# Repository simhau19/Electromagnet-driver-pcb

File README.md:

# Electromagnet-driver-pcb
[Schematics](Audiovisualizer%20PCB.pdf)

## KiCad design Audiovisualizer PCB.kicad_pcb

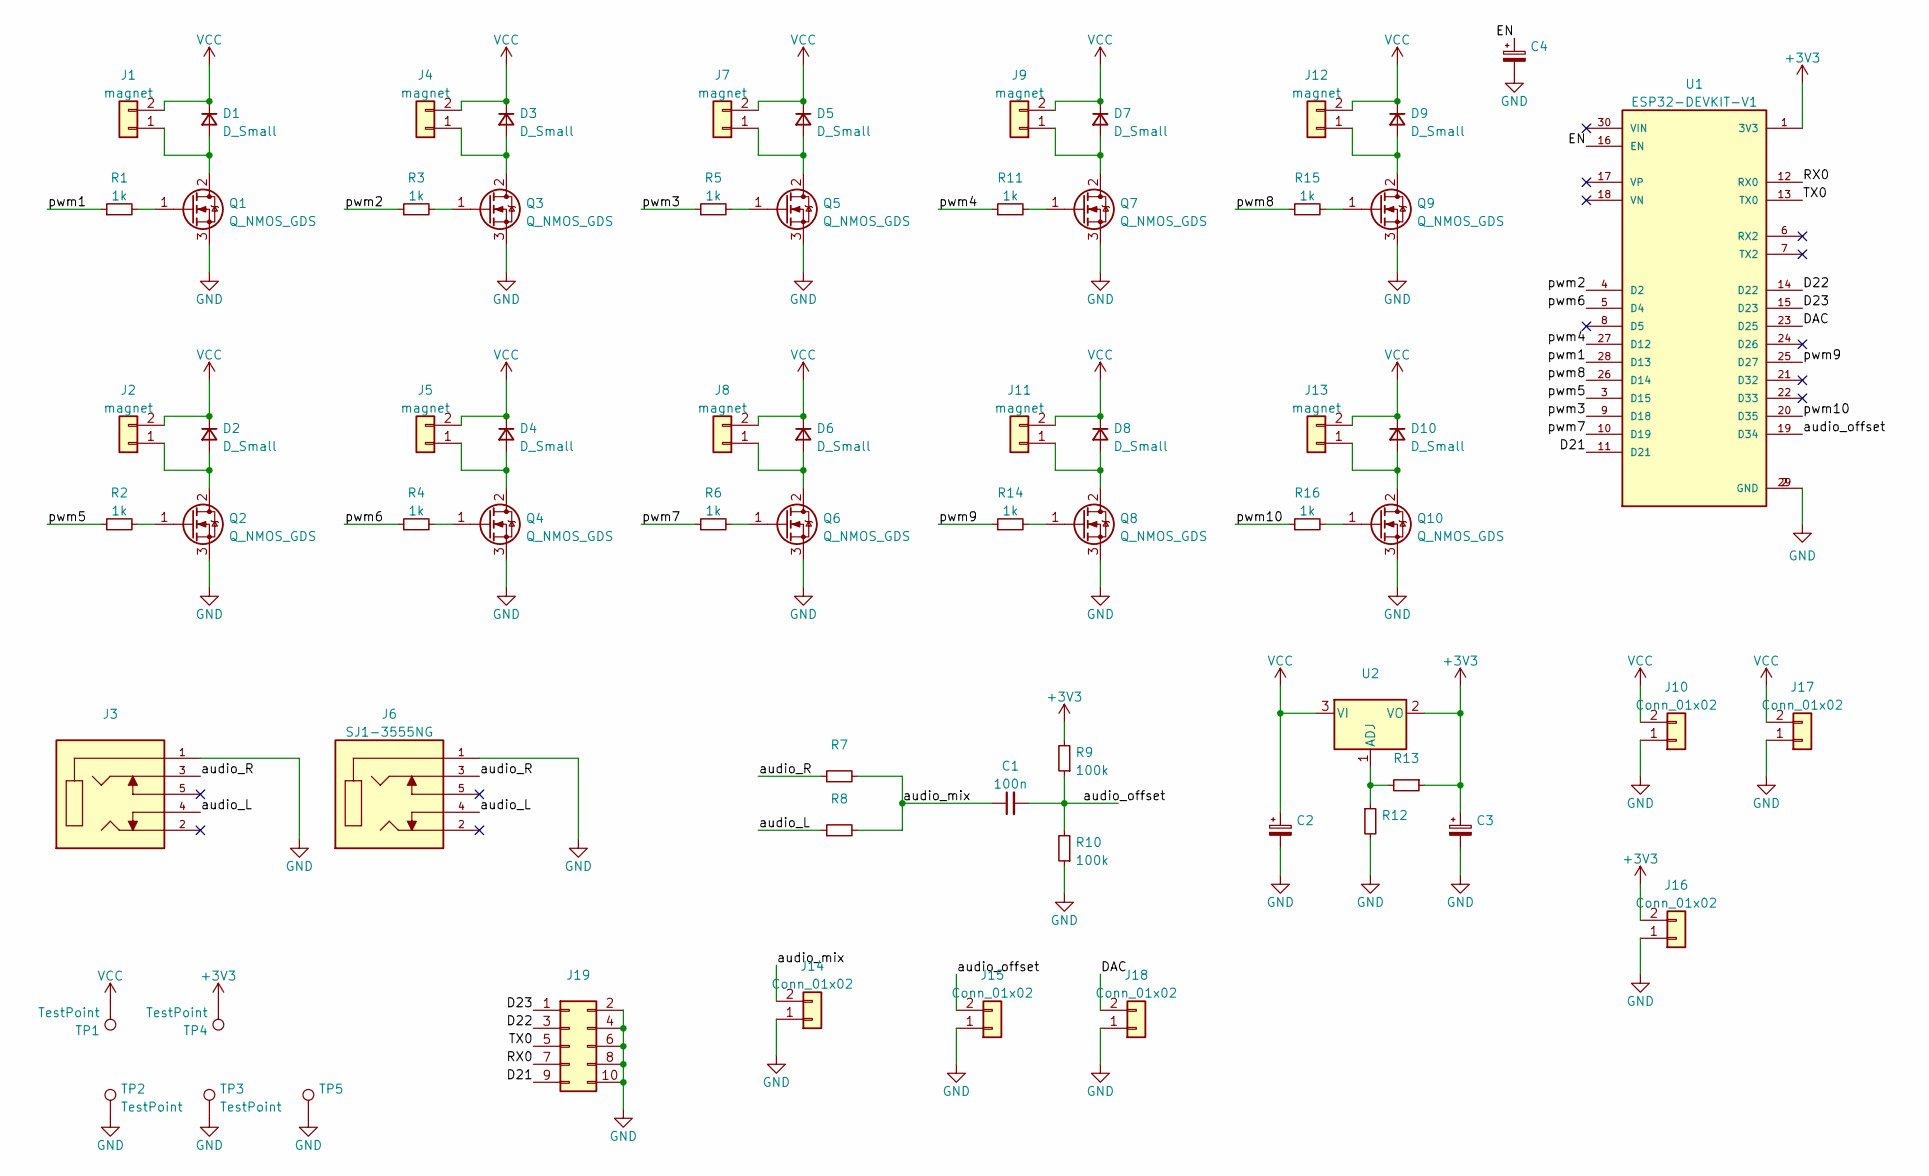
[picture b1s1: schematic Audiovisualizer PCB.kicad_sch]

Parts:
C1: 100n
C2, C3: (no value)
C4: CP_Radial_D6.3mm_P2.50mm
D1, D2, D3, D4, D5, D6, D7, D8, D9, D10: D_Small; D_A-405_P7.62mm_Horizontal
J1, J2, J4, J5, J7, J8, J9, J11, J12, J13: magnet; PinHeader_1x02_P2.54mm_Vertical
J3: PART_REV 1.0
J6: SJ1-3555NG; PART_REV 1.0
J10, J14, J15, J16, J18: Conn_01x02; PinHeader_1x02_P2.54mm_Vertical
J17: Conn_01x02
J19: (no value)
Q1, Q2, Q3, Q4, Q5, Q6, Q7, Q8, Q9, Q10: Q_NMOS_GDS; TO-220-3_Vertical
R1, R2, R3, R4, R5, R6, R11, R14, R15, R16: 1k; R_Axial_DIN0204_L3.6mm_D1.6mm_P7.62mm_Horizontal
R7, R8: R_Axial_DIN0204_L3.6mm_D1.6mm_P7.62mm_Horizontal
R9, R10: 100k; R_Axial_DIN0204_L3.6mm_D1.6mm_P7.62mm_Horizontal
R12, R13: (no value)
TP1, TP2, TP3, TP4: TestPoint
TP5: (no value)
U1: ESP32-DEVKIT-V1; MODULE_ESP32_DEVKIT_V1; PARTREV N/A
U2: (no value)

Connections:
+3V3: C3.1, J16.2, R9.2, R13.1, TP4.1, U1.1 (3V3), U2.2 (VO)
/D21: J19.9, U1.11 (D21)
/D22: J19.3, U1.14 (D22)
/D23: J19.1, U1.15 (D23)
/DAC: J18.2, U1.23 (D25)
/EN: C4.1, U1.16 (EN)
/RX0: J19.7, U1.12 (RX0)
/TX0: J19.5, U1.13 (TX0)
/audio_L: J3.4, J6.4, R8.1
/audio_R: J3.3, J6.3, R7.1
/audio_mix: C1.1, J14.2, R7.2, R8.2
/audio_offset: C1.2, J15.2, R9.1, R10.2, U1.19 (D34)
/pwm1: R1.1, U1.28 (D13)
/pwm2: R3.1, U1.4 (D2)
/pwm3: R5.1, U1.9 (D18)
/pwm4: R11.1, U1.27 (D12)
/pwm5: R2.1, U1.3 (D15)
/pwm6: R4.1, U1.5 (D4)
/pwm7: R6.1, U1.10 (D19)
/pwm8: R15.1, U1.26 (D14)
/pwm9: R14.1, U1.25 (D27)
/pwm10: R16.1, U1.20 (D35)
GND: C2.2, C3.2, C4.2, J3.1, J6.1, J10.1, J14.1, J15.1, J16.1, J17.1, J18.1, J19.2, J19.4, J19.6, J19.8, J19.10, Q1.3 (S), Q2.3 (S), Q3.3 (S), Q4.3 (S), Q5.3 (S), Q6.3 (S), Q7.3 (S), Q8.3 (S), Q9.3 (S), Q10.3 (S), R10.1, R12.2, TP2.1, TP3.1, TP5.1, U1.2 (GND), U1.29 (GND)
unnamed: D1.2 (A), J1.1, Q1.2 (D)
unnamed: D2.2 (A), J2.1, Q2.2 (D)
unnamed: D3.2 (A), J4.1, Q3.2 (D)
unnamed: D4.2 (A), J5.1, Q4.2 (D)
unnamed: D5.2 (A), J7.1, Q5.2 (D)
unnamed: D6.2 (A), J8.1, Q6.2 (D)
unnamed: D7.2 (A), J9.1, Q7.2 (D)
unnamed: D8.2 (A), J11.1, Q8.2 (D)
unnamed: D9.2 (A), J12.1, Q9.2 (D)
unnamed: D10.2 (A), J13.1, Q10.2 (D)
unnamed: Q1.1 (G), R1.2
unnamed: Q2.1 (G), R2.2
unnamed: Q3.1 (G), R3.2
unnamed: Q4.1 (G), R4.2
unnamed: Q5.1 (G), R5.2
unnamed: Q6.1 (G), R6.2
unnamed: Q7.1 (G), R11.2
unnamed: Q8.1 (G), R14.2
unnamed: Q9.1 (G), R15.2
unnamed: Q10.1 (G), R16.2
unnamed: R12.1, R13.2, U2.1 (ADJ)
VCC: C2.1, D1.1 (K), D2.1 (K), D3.1 (K), D4.1 (K), D5.1 (K), D6.1 (K), D7.1 (K), D8.1 (K), D9.1 (K), D10.1 (K), J1.2, J2.2, J4.2, J5.2, J7.2, J8.2, J9.2, J10.2, J11.2, J12.2, J13.2, J17.2, TP1.1, U2.3 (VI)

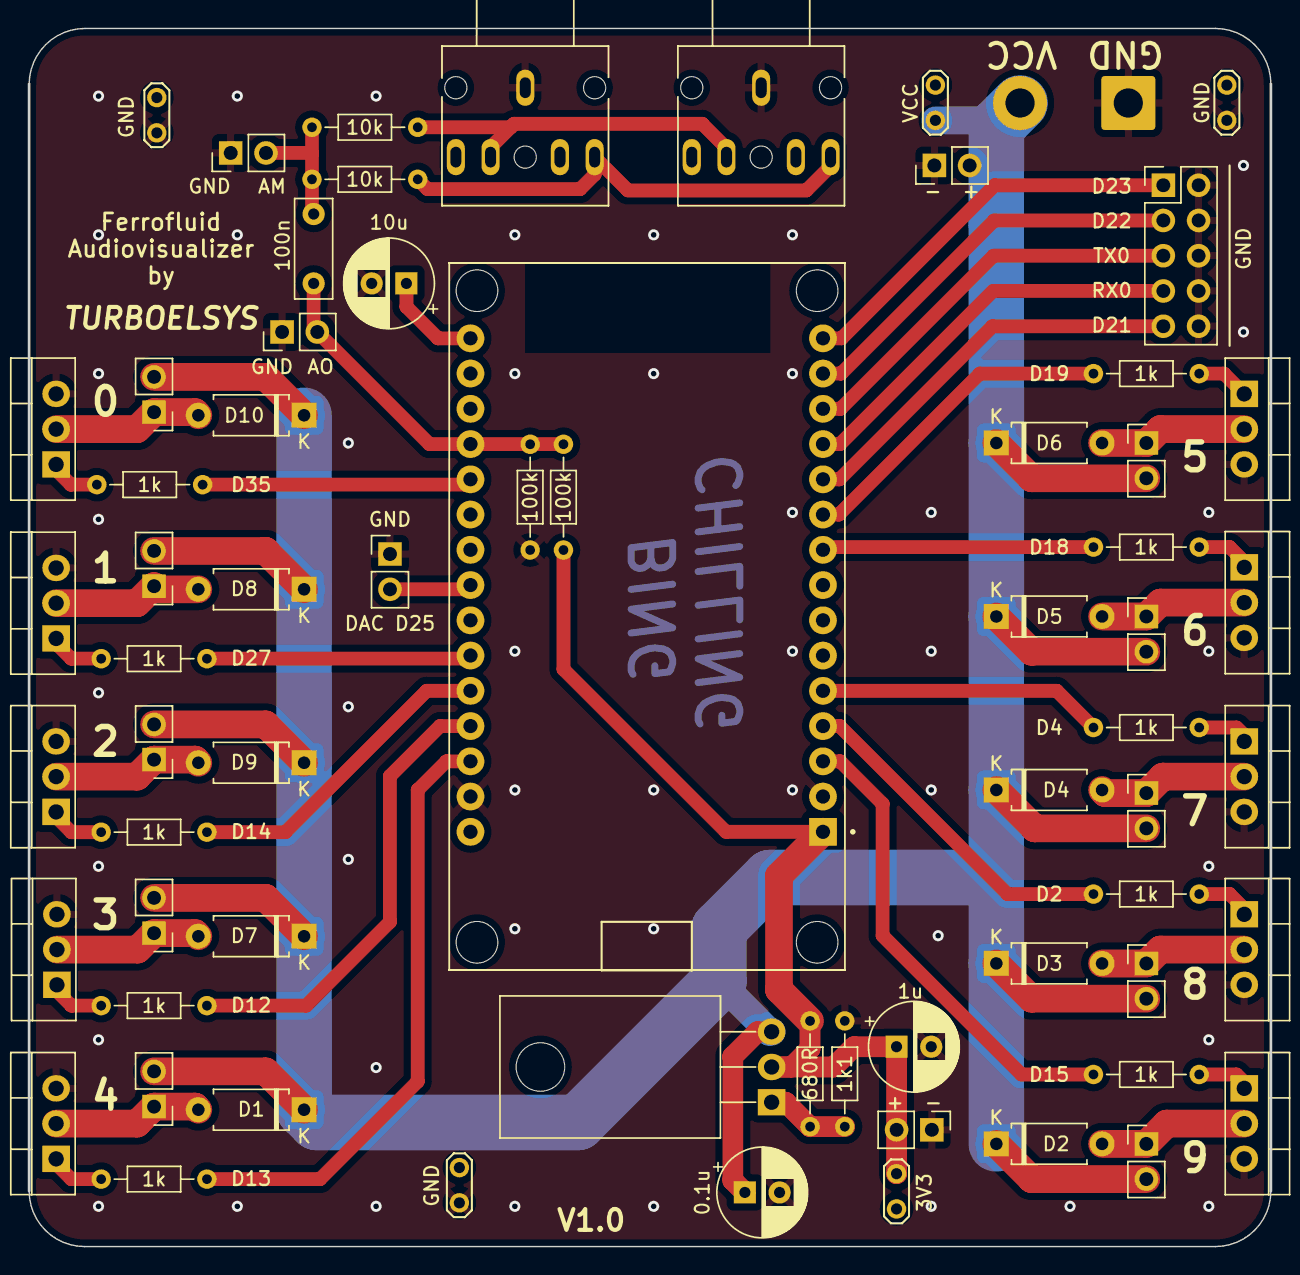
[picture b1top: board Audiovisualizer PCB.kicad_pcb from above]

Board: 2 copper layers, 89.5 x 87.7 mm, 66 parts (0 on the bottom side), 45 nets.

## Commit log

2023-04-13 added component values
2023-04-24 updated pdf
